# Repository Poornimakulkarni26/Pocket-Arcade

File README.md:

# Pocket Arcade 🕹️

A fist-sized handheld game console built from scratch — custom PCB, 10+ games, OLED display, rechargeable battery, and tactile controls. Designed and fabricated entirely from scratch using KiCad.

---

## Overview

This is a fully custom-designed handheld game console — small enough to fit in your fist. Every part of it, from the PCB layout to the game logic, was built from the ground up. 
It runs 10+ games stored on an SD card, displays them on a 1.3" OLED screen, and is powered by a rechargeable lithium battery that charges over USB via a TP4056 module.

---

## Games

| Game | Description |
|---|---|
| 🐍 Snake | Classic grow-the-snake maze game |
| 🧱 Tetris | Falling block puzzle |
| 🏓 Pong | Two-paddle ball game |
| 🚗 Car Race | Dodge oncoming traffic |
| 🦕 Dinosaur | Endless runner, jump over obstacles |

---

## Hardware

| Component | Details |
|---|---|
| Microcontroller | RP2040 (Dual-core Arm Cortex-M0+, 133 MHz) |
| Display | 1.3" OLED (SSD1306/SH1106) |
| Controls | Tactile switches — Up, Down, Left, Right, A, B |
| Storage | SD card (game assets and save data) |
| Battery | Lithium-ion rechargeable |
| Charging | TP4056 USB charging module |
| Form factor | Fist-sized, fully handheld |

---

## PCB Design Highlights

- **Compact layout** — everything packed into a fist-sized footprint without sacrificing signal integrity
- **RP2040 as the brain** — dual-core gives one core to game logic and the other to display rendering, keeping gameplay smooth
- **1.3" OLED over SPI/I2C** — crisp display with low power draw, perfect for battery-powered handheld use
- **SD card storage** — games and assets stored externally, easy to update without reflashing firmware
- **TP4056 charging circuit** — safe single-cell Li-ion charging with overcharge and over-discharge protection built in
- **Tactile switches** — low-profile, responsive buttons for directional and action input

---

## Getting Started

### View the Design
1. Install [KiCad](https://www.kicad.org/) (v7+ recommended)
2. Clone this repo:
   ```bash
   git clone https://github.com/Poornimakulkarni26/pocket-arcade.git
   ```
3. Open the `.kicad_pro` file in KiCad

### Flash a Game
1. Copy game `.uf2` or binary files onto the SD card
2. Insert SD card into the console
3. Power on — select game from the menu

---

## What I Learned

- Designing a compact mixed-signal PCB with power, digital, and display circuits on one board
- Managing battery power and USB charging safely with the TP4056 module
- Using RP2040's dual-core architecture to separate game logic from display rendering
- Routing SPI/I2C traces cleanly in a space-constrained layout
- Building and playing actual games on hardware I designed myself 🎮

---

## Author

**Poornima Kulkarni**
Embedded Systems Engineer

- GitHub: [@Poornimakulkarni26](https://github.com/Poornimakulkarni26)

---

## License

This project is open-source under the [MIT License](LICENSE).

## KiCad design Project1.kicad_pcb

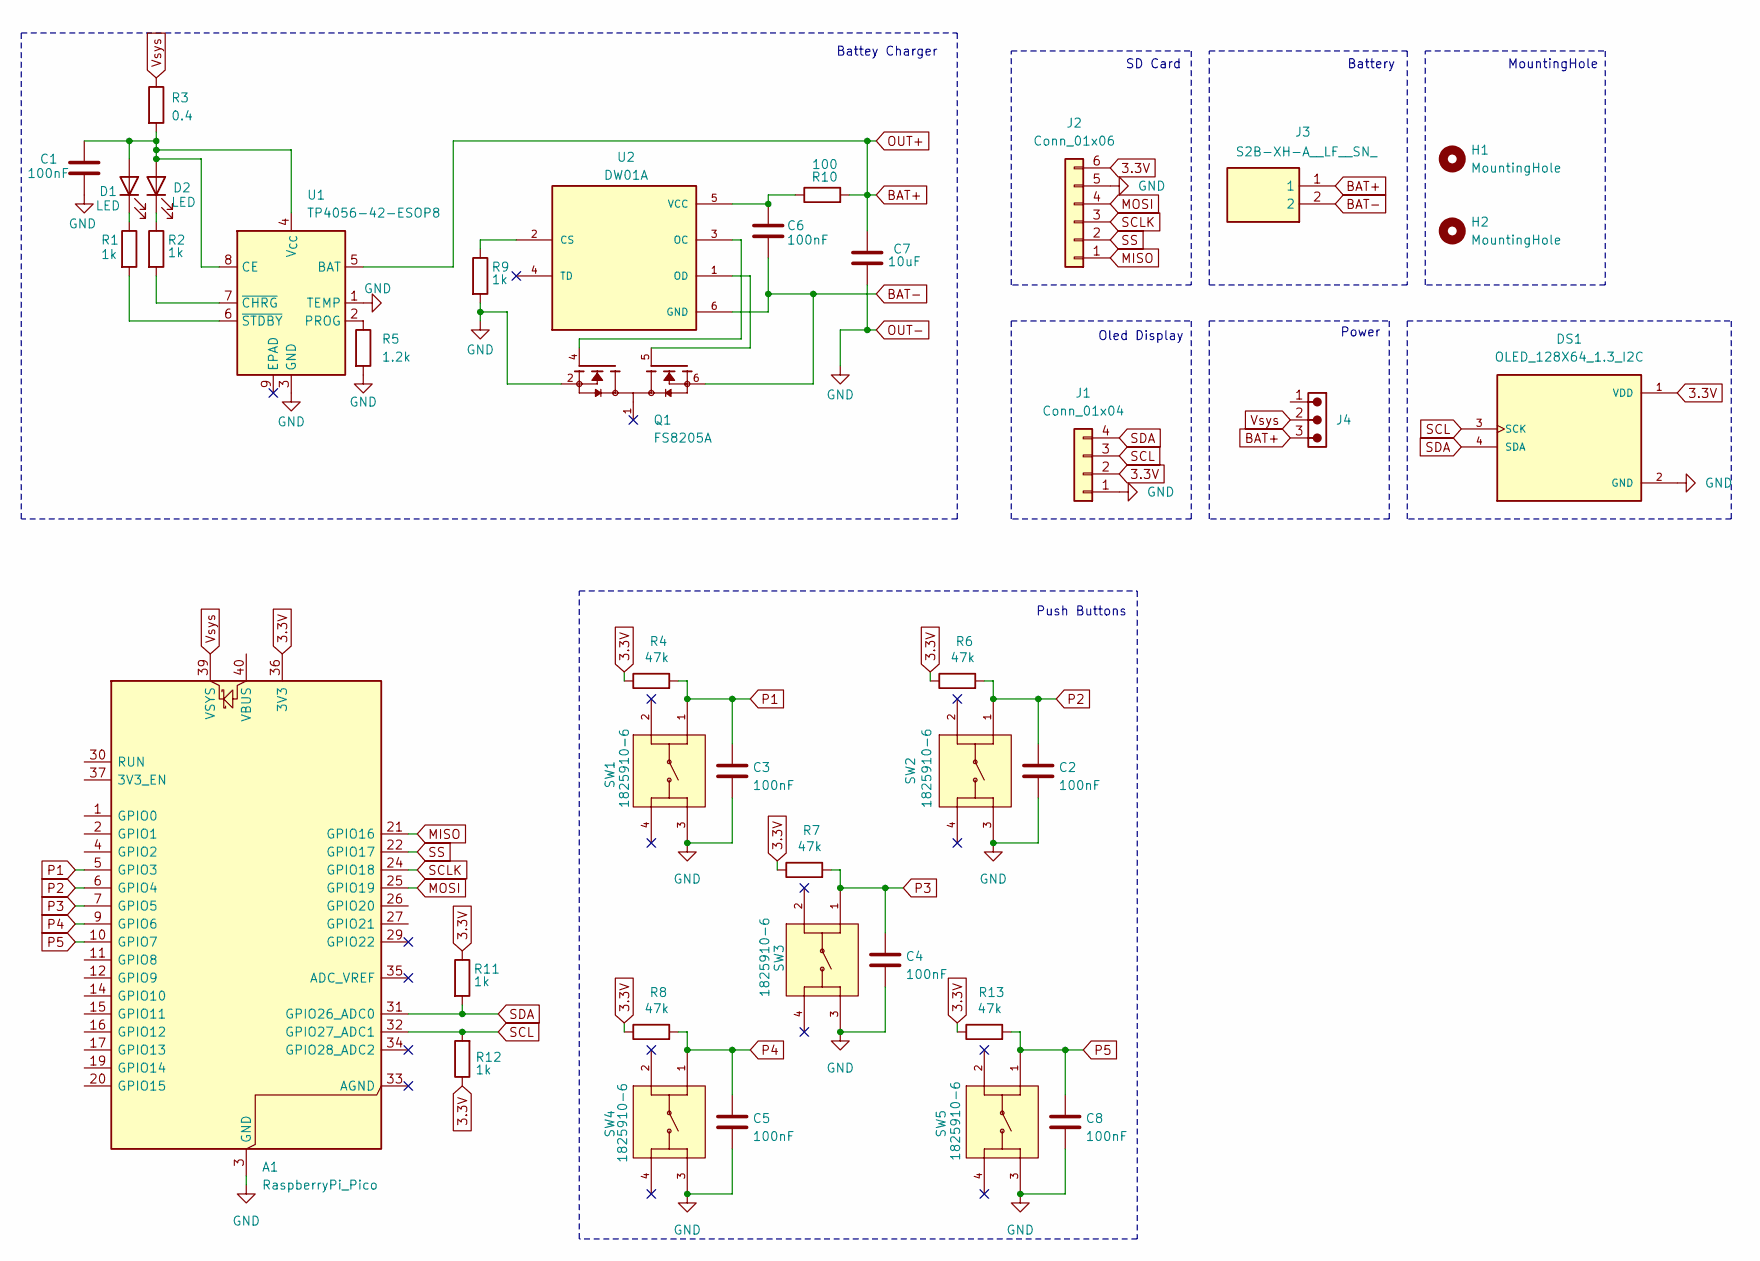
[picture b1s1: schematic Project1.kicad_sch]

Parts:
A1: RaspberryPi_Pico; RaspberryPi_Pico_Common_Unspecified
C1, C2, C3, C4, C5, C6, C8: 100nF; C_0603_1608Metric_Pad1.08x0.95mm_HandSolder
C7: 10uF; C_0603_1608Metric_Pad1.08x0.95mm_HandSolder
D1, D2: LED; LED_0603_1608Metric_Pad1.05x0.95mm_HandSolder
DS1: OLED_128X64_1.3_I2C; LCD_OLED_128X64_1.3_I2C; PARTREV NA
H1, H2: MountingHole; MountingHole_2.2mm_M2
J1: Conn_01x04; PinHeader_1x04_P2.54mm_Vertical
J2: Conn_01x06; PinHeader_1x06_P2.54mm_Vertical
J3: S2B-XH-A__LF__SN_; JST_XH_S2B-XH-A-1_1x02_P2.50mm_Horizontal; Manufacturer_Part_Number S2B-XH-A (LF)(SN)
J4: 68800311622; J_Wurth_WR-WTB_68800311622; Working Voltage (V (AC)) 250
Q1: FS8205A; SOP65P640X120-8N; PARTREV 1.7
R1, R2, R9, R11, R12: 1k; R_0603_1608Metric_Pad0.98x0.95mm_HandSolder
R3: 0.4; R_0603_1608Metric_Pad0.98x0.95mm_HandSolder
R4, R6, R7, R8, R13: 47k; R_0603_1608Metric_Pad0.98x0.95mm_HandSolder
R5: 1.2k; R_0603_1608Metric_Pad0.98x0.95mm_HandSolder
R10: 100; R_0603_1608Metric_Pad0.98x0.95mm_HandSolder
SW1, SW2, SW3, SW4, SW5: 1825910-6; SW_1825910-6-4; PARTREV C10
U1: TP4056-42-ESOP8; SOIC-8-1EP_3.9x4.9mm_P1.27mm_EP2.41x3.3mm_ThermalVias
U2: DW01A; SOT95P280X145-6N; PARTREV 1.8

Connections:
3.3V: A1.36 (3V3), DS1.1 (VDD), J1.2, J2.6, R4.1, R6.1, R7.1, R8.1, R11.1, R12.1, R13.1
BAT+: C7.1, J3.1, J4.3, R10.2, U1.5 (BAT)
BAT-: C6.2, J3.2, Q1.6, Q1.7, U2.6 (GND)
MISO: A1.21 (GPIO16), J2.1
MOSI: A1.25 (GPIO19), J2.4
unnamed: C1.1, D1.2 (A), D2.2 (A), R3.2, U1.4 (V_{CC}), U1.8 (CE)
unnamed: D1.1 (K), R1.1
unnamed: D2.1 (K), R2.1
unnamed: R5.1, U1.2 (PROG)
unnamed: R2.2, U1.7 (~CHRG)
unnamed: R1.2, U1.6 (~STDBY)
unnamed: R9.1, U2.2 (CS)
unnamed: Q1.4, U2.3 (OC)
unnamed: Q1.5, U2.1 (OD)
unnamed: C6.1, R10.1, U2.5 (VCC)
OUT-: A1.3 (GND), A1.8 (GND), A1.13 (GND), A1.18 (GND), A1.23 (GND), A1.28 (GND), A1.38 (GND), C1.2, C2.2, C3.2, C4.2, C5.2, C7.2, C8.2, DS1.2 (GND), J1.1, J2.5, Q1.2, Q1.3, R5.2, R9.2, SW1.3, SW2.3, SW3.3, SW4.3, SW5.3, U1.1 (TEMP), U1.3 (GND)
P1: A1.5 (GPIO3), C3.1, R4.2, SW1.1
P2: A1.6 (GPIO4), C2.1, R6.2, SW2.1
P3: A1.7 (GPIO5), C4.1, R7.2, SW3.1
P4: A1.9 (GPIO6), C5.1, R8.2, SW4.1
P5: A1.10 (GPIO7), C8.1, R13.2, SW5.1
SCL: A1.32 (GPIO27_ADC1), DS1.3 (SCK), J1.3, R12.2
SCLK: A1.24 (GPIO18), J2.3
SDA: A1.31 (GPIO26_ADC0), DS1.4 (SDA), J1.4, R11.2
SS: A1.22 (GPIO17), J2.2
Vsys: A1.39 (VSYS), J4.2, R3.1

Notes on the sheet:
Oled Display
Power
MountingHole
Push Buttons
Battery
Battey Charger
SD Card

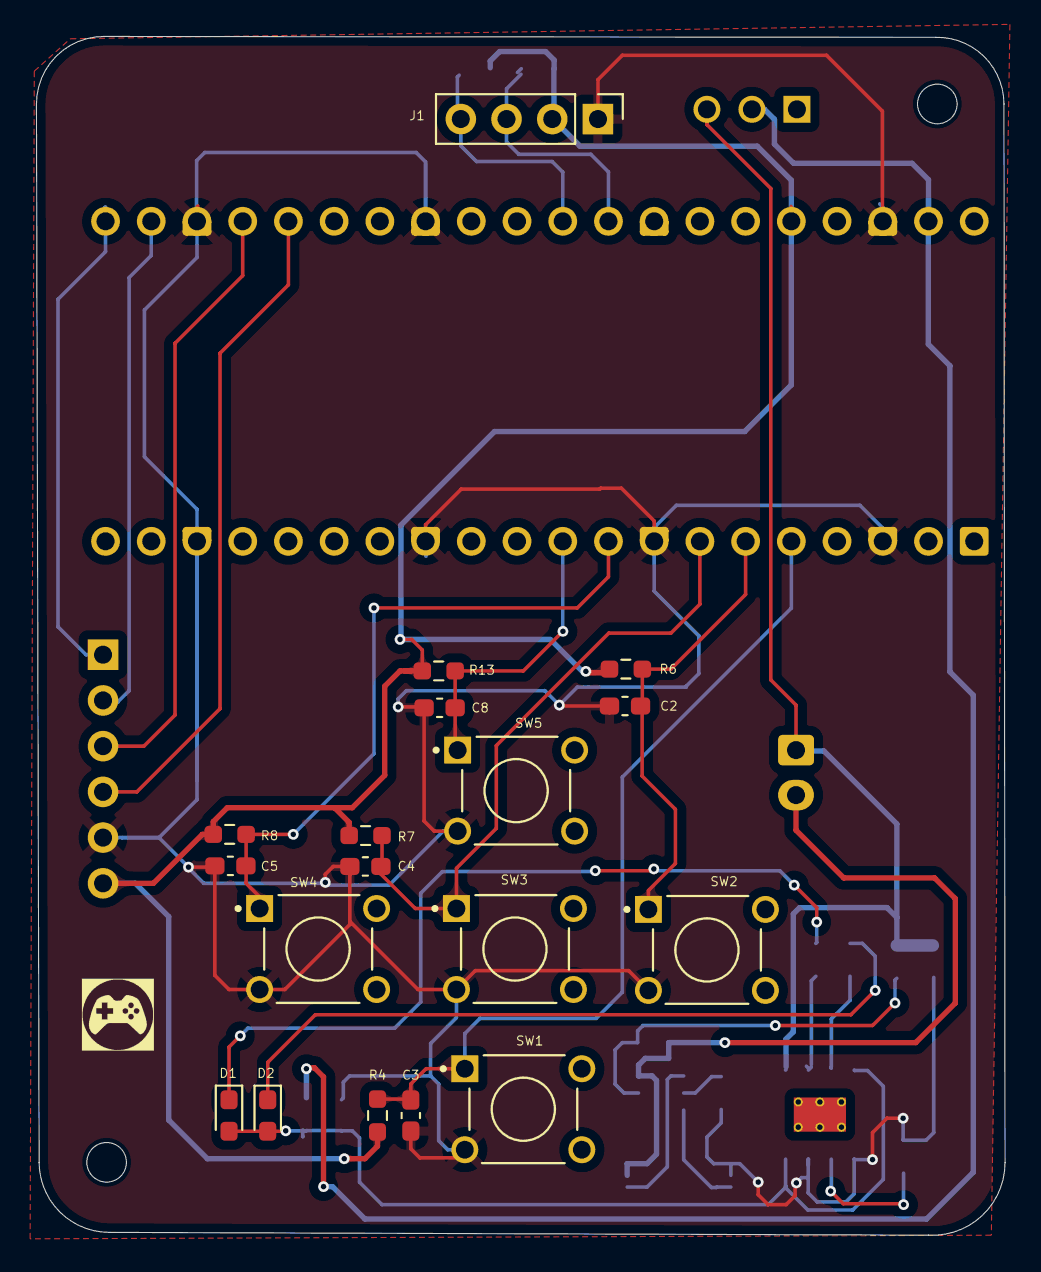
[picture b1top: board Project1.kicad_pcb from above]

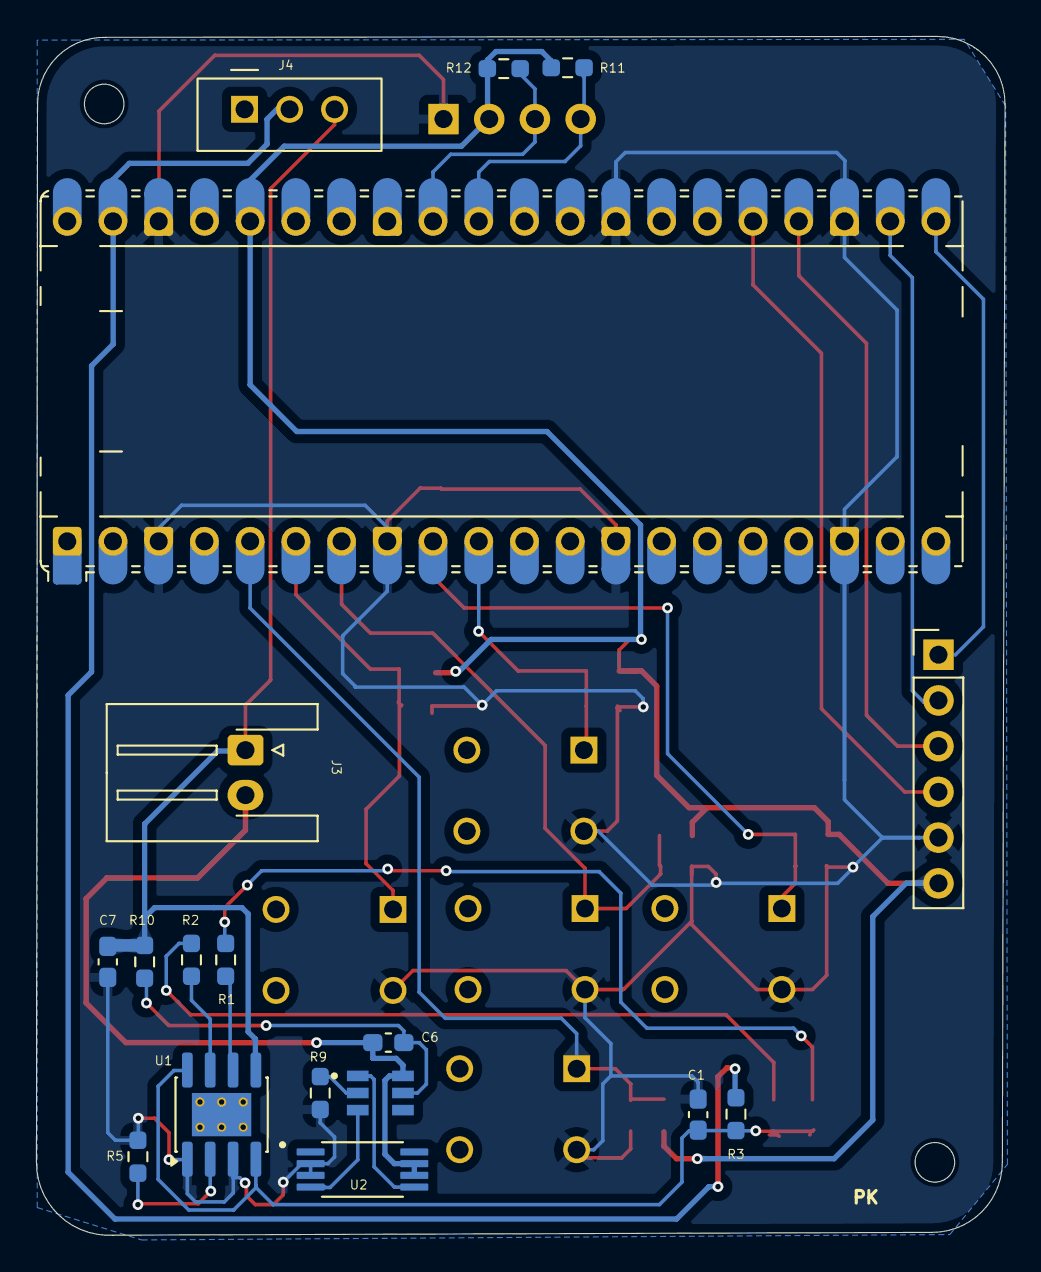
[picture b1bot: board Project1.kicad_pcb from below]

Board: 2 copper layers, 53.8 x 66.6 mm, 38 parts (18 on the bottom side), 26 nets.
